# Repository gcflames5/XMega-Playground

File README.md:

XMega Playground
====

Overview
----
This board serves as a place where users can practice various aspects of embedded programming using an XMega(128/64/32)A4U. The first version of this board is focused heavily on testing various types of communication protocols, featuring USB, Serial, CAN, SPI, and I2C. Additionally, the board includes a pair of 7 segment displays, and 10 LEDs (4 are digital RGB LEDs) to allow a degree of output to the user. For use with these various communication protocols, this board includes an separate ADC (with pressure and temperature sensors), flash memory IC, TTL to RS-232 level shifter, CAN transciever, and two IMUs.

List of Features (version 1.0)
----
 - 2 7-segment displays (driven by shift registers)
 - 4 WS2812B digital RHB leds
 - 6 0805 LEDs
 - CAN Transciever
 - RS-232 to TTL level shifter
 - 2 IMUs: Acceleration, Magetometer
 - ADC (w/ 2.5V reference chip)
   - Temperature sensor
   - Ambient pressure sensor
 - Flash Memory
 - Current Sense Op Amp
   - Configurable load for testing

Considerations for Future Versions
----
 - Add a character LCD display for more useful output to the user
 - Break out more GPIO pins into headers
 - Expand number of 7 segment displays
 - Utilize DAC and waveform generation, include H-bridge, microphone, speaker, etc.

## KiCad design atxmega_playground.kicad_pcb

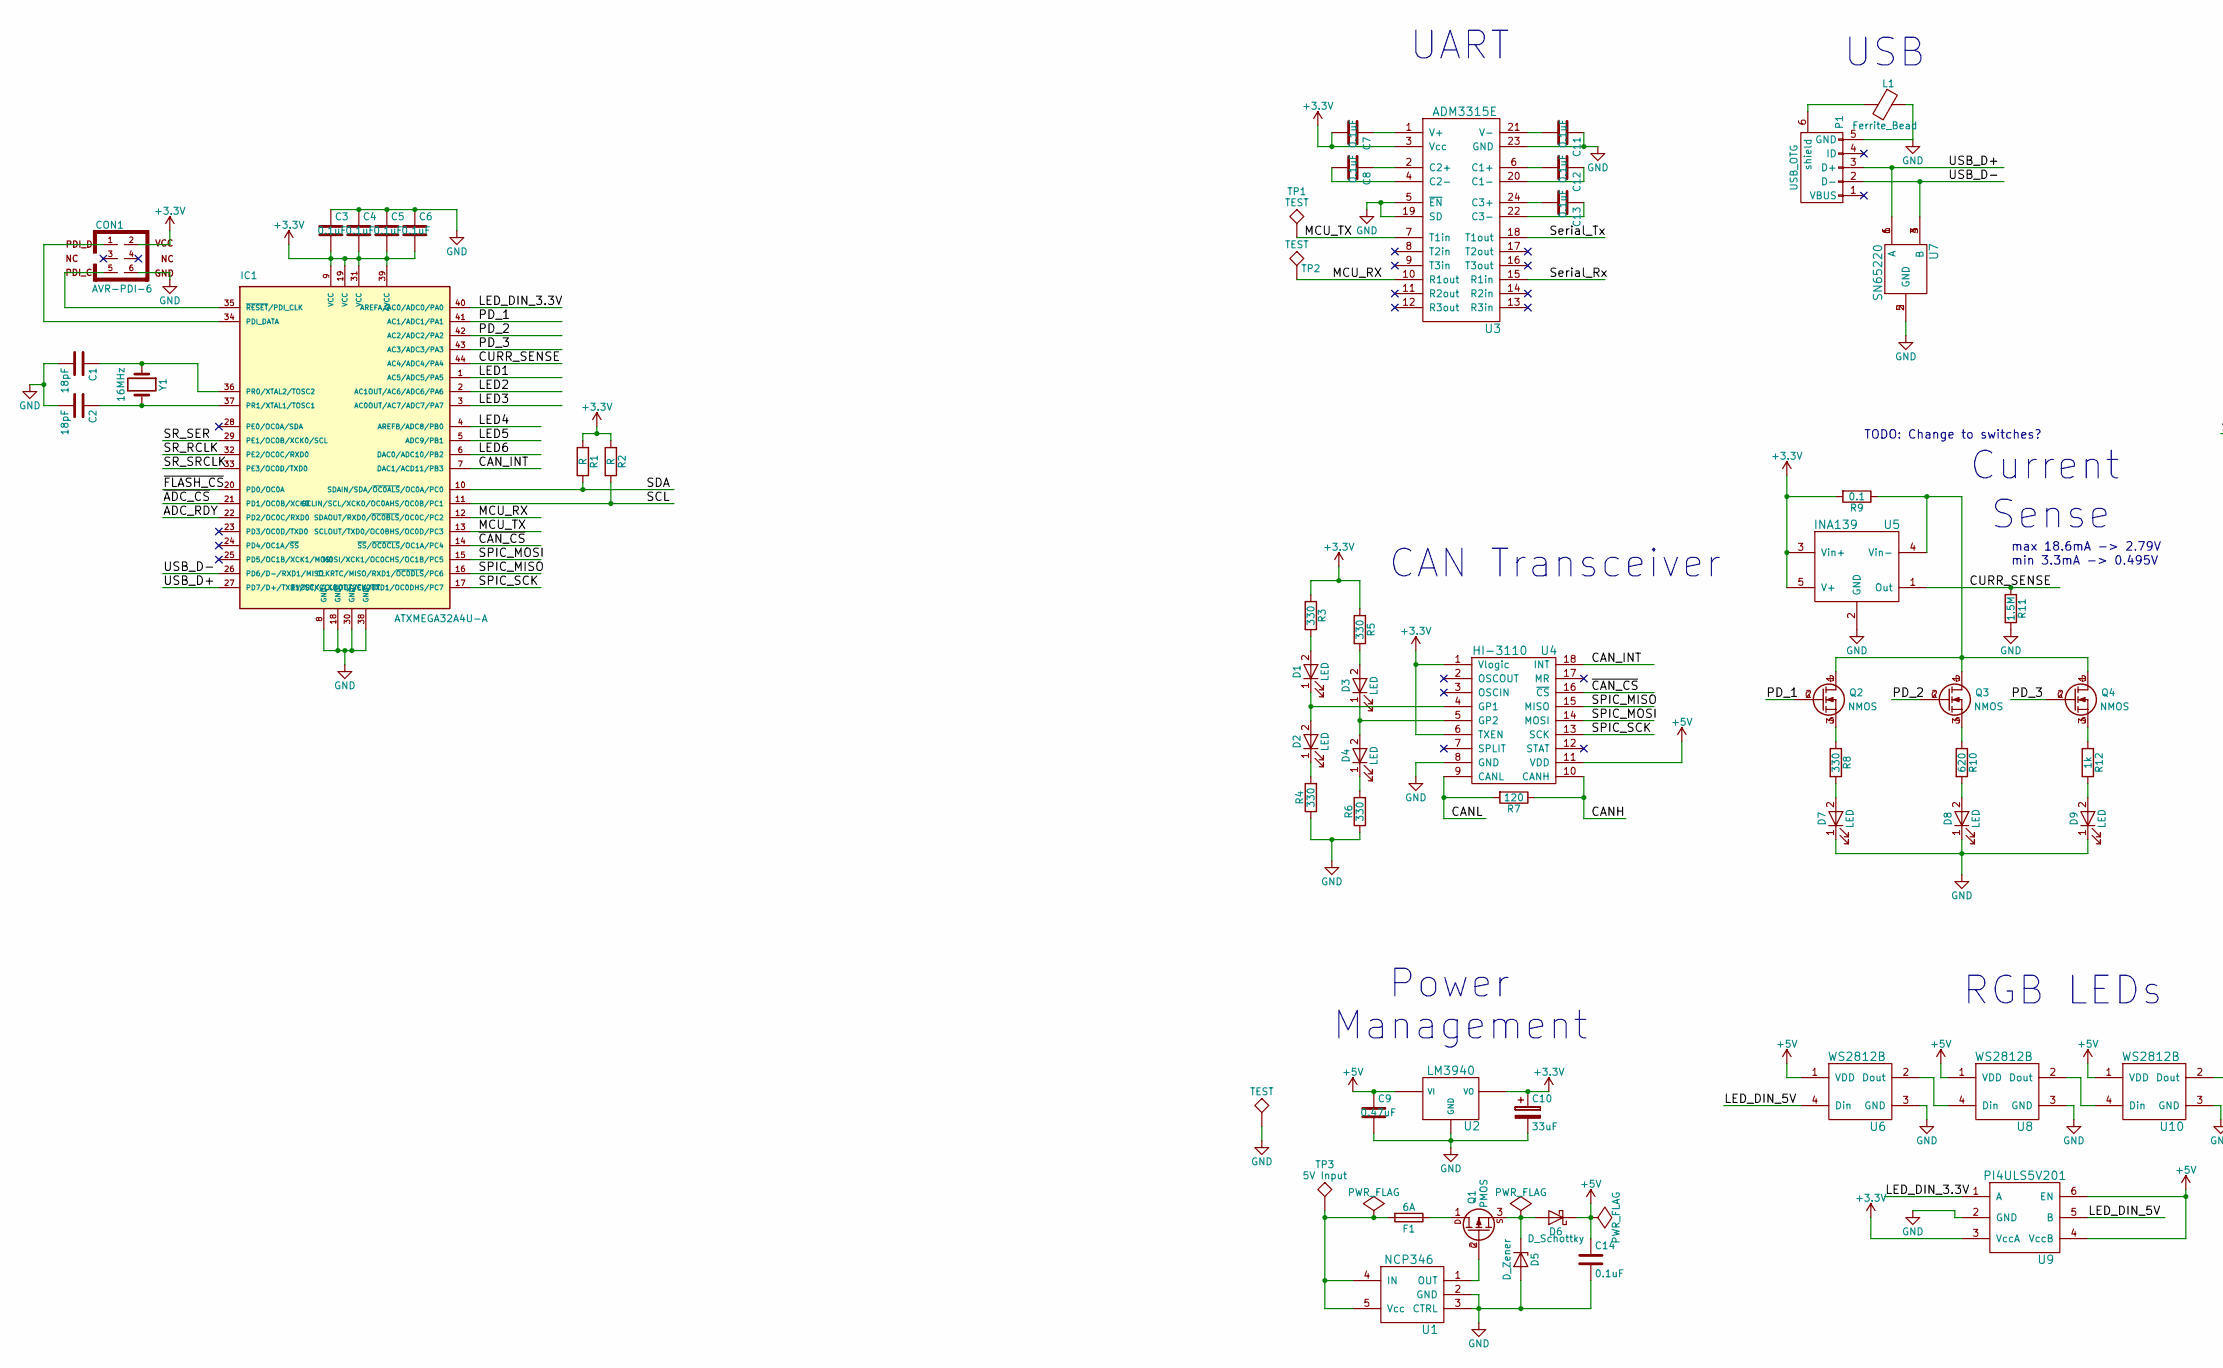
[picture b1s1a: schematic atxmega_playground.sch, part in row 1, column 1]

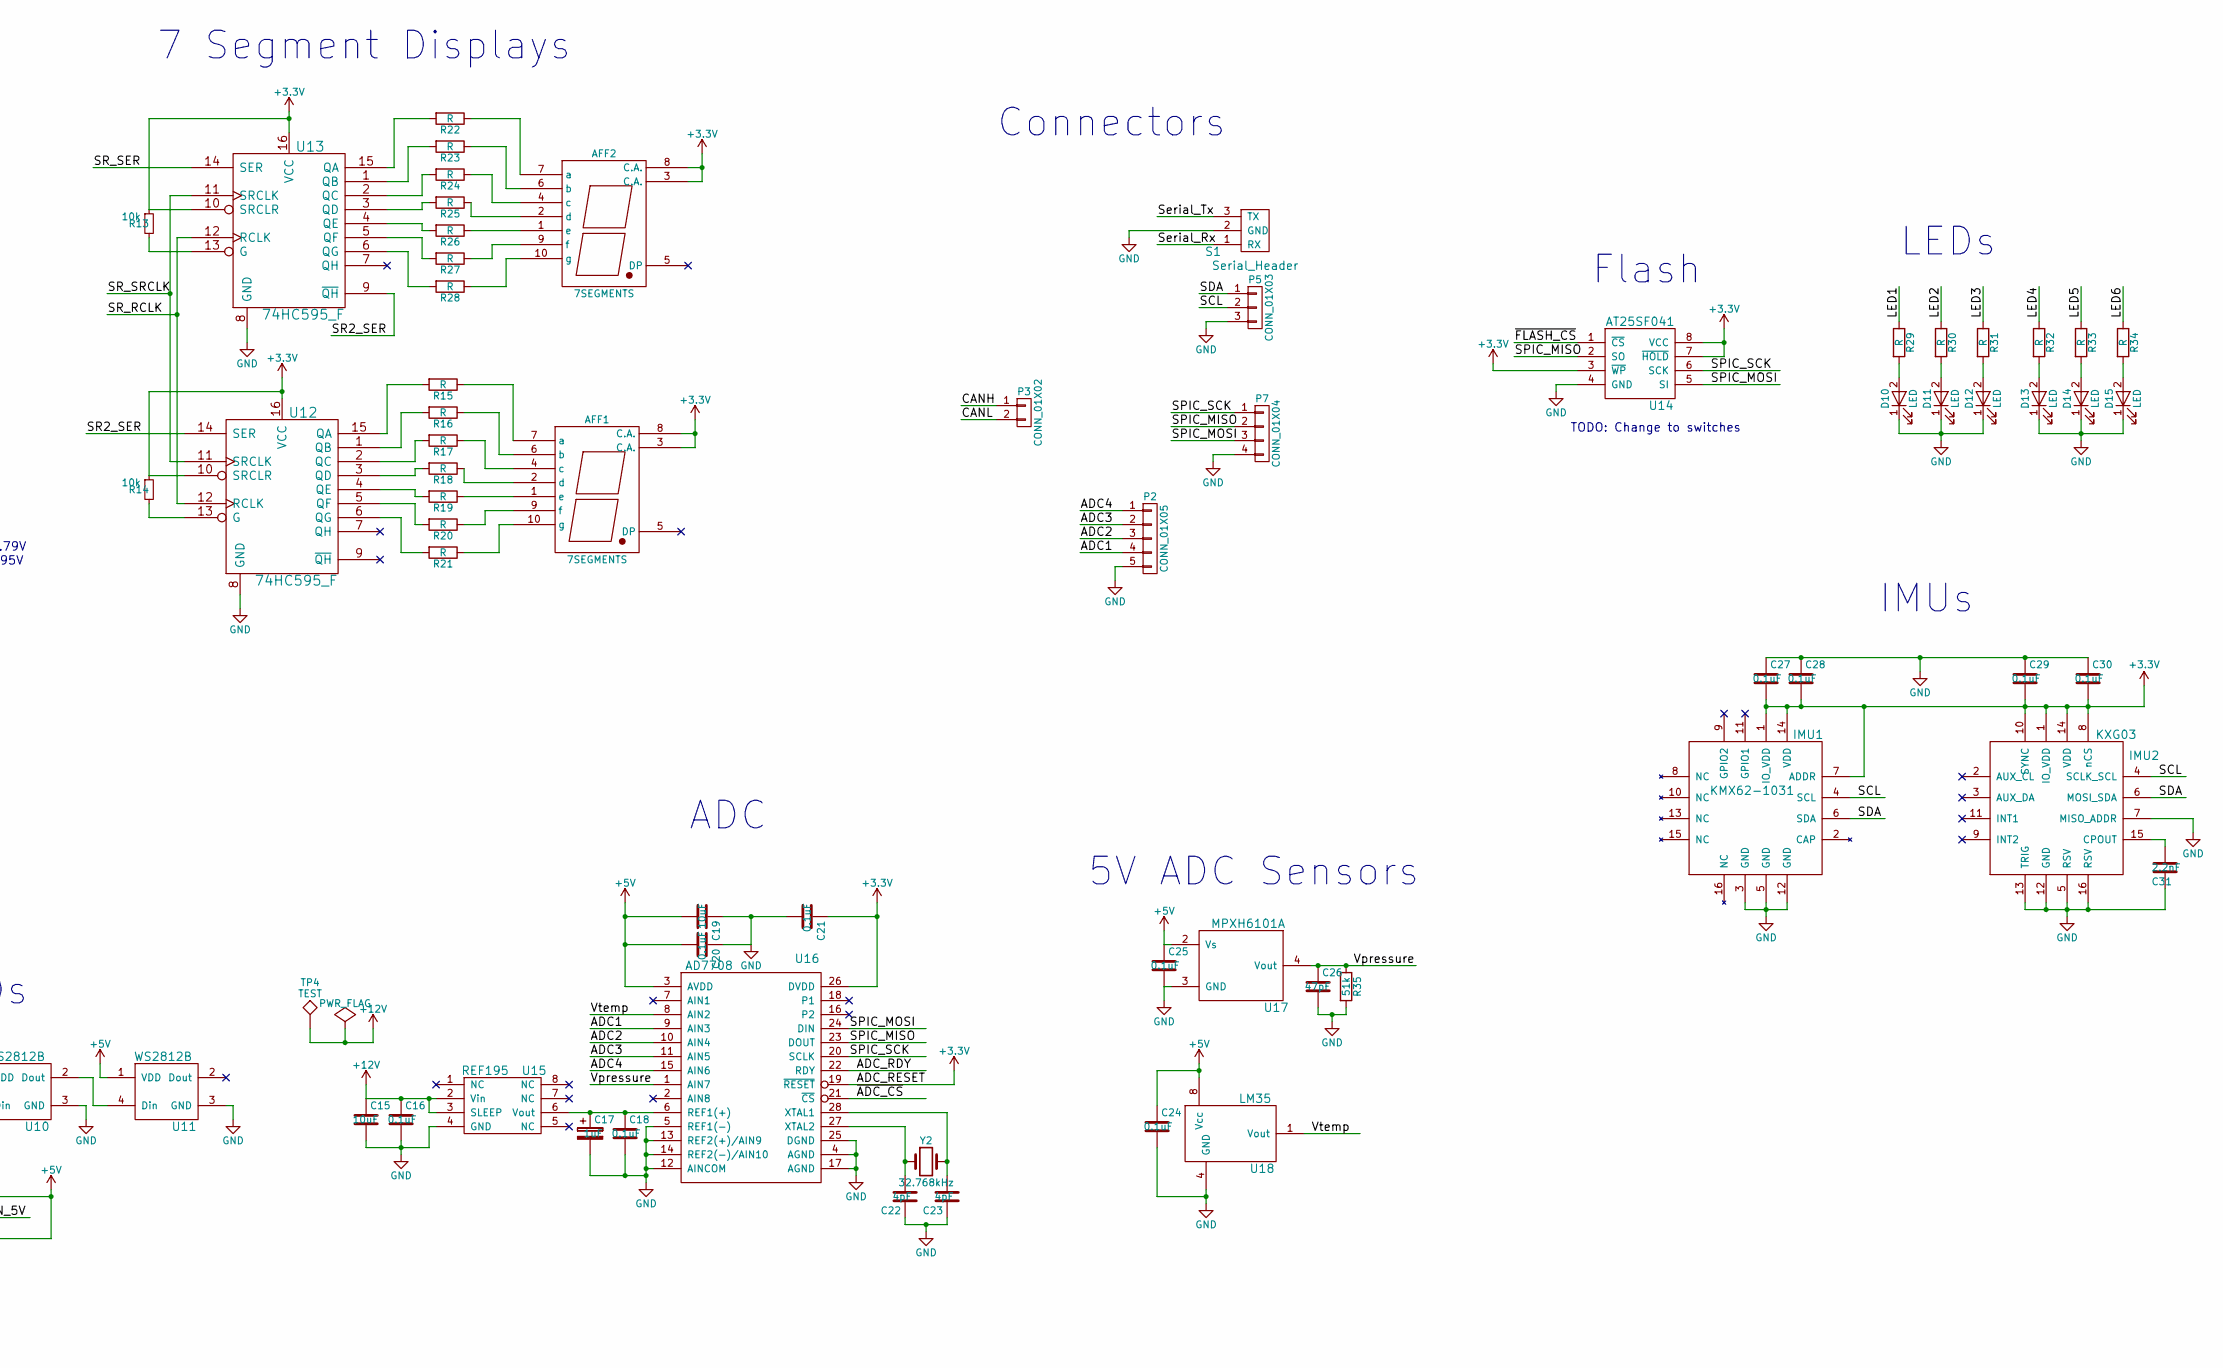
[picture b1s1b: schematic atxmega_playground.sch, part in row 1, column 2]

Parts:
AFF1, AFF2: 7SEGMENTS; 7seg_SC56-11SRWA
C1, C2: 18pF; C_0805
C3, C4, C5, C6, C7, C8, C11, C12, C13, C14, C16, C18, C20, C21, C24, C25, C27, C28, C29, C30: 0.1uF; C_0805
C9: 0.47uF; C_0805
C10: 33uF; R_1206
C15, C19: 10uF; C_0805
C17: 1uF; R_1206
C22, C23: 4pF; C_0805
C26: 47pF; C_0805
C31: 2.2nF; C_0805
CON1: AVR-PDI-6; Pin_Header_Straight_2x03_Pitch2.54mm
D1, D2, D3, D4, D7, D8, D9, D10, D11, D12, D13, D14, D15: LED; LED_0805
D5: D_Zener; SOD-123
D6: D_Schottky; R_0805
F1: 6A; R_1206
IC1: ATXMEGA32A4U-A; TQFP-44_10x10mm_Pitch0.8mm
IMU1: KMX62-1031; KXG03_footprint
IMU2: KXG03; KXG03_footprint
L1: Ferrite_Bead; R_0805
P1: USB_OTG; USB_Mini-B
P2: CONN_01X05; Pin_Header_Straight_1x05_Pitch2.54mm
P3: CONN_01X02; Pin_Header_Straight_1x02_Pitch2.54mm
P5: CONN_01X03; Pin_Header_Straight_1x03_Pitch2.54mm
P7: CONN_01X04; Pin_Header_Straight_1x04_Pitch2.54mm
Q1: PMOS; SOT-23-3_Handsoldering
Q2, Q3, Q4: NMOS; SOT-23-3_Handsoldering
R1, R2, R15, R16, R17, R18, R19, R20, R21, R22, R23, R24, R25, R26, R27, R28, R29, R30, R31, R32, R33, R34: R; R_0805
R3, R4, R5, R6, R8: 330; R_0805
R7: 120; R_0805
R9: 0.1; R_0805
R10: 620; R_0805
R11: 1.5M; R_0805
R12: 1k; R_0805
R13, R14: 10k; R_0805
R35: 51k; R_0805
S1: Serial_Header; Pin_Header_Straight_1x03_Pitch2.54mm
TP1, TP2, TP4, TP5: TEST; TESTPOINT
TP3: 5V Input; TESTPOINT
U1: NCP346; SOT-23-5
U2: LM3940; SOT-223
U3: ADM3315E; TSSOP-24_4.4x7.8mm_Pitch0.65mm
U4: HI-3110; SOIC-18W_7.5x11.6mm_Pitch1.27mm
U5: INA139; SOT-23-5
U6, U8, U10, U11: WS2812B
U7: SN65220; SOT-23-6
U9: PI4ULS5V201; SOT-23-6
U12, U13: 74HC595_F; SOIC-16_3.9x9.9mm_Pitch1.27mm
U14: AT25SF041; SOIC-8_3.9x4.9mm_Pitch1.27mm
U15: REF195; SOIC-8_3.9x4.9mm_Pitch1.27mm
U16: AD7708; SOIC-28W_7.5x17.9mm_Pitch1.27mm
U17: MPXH6101A; SOIC-8_7.5x7.5mm_Pitch1.27mm
U18: LM35; SOIC-8_3.9x4.9mm_Pitch1.27mm
Y1: 16MHz; Crystal_HC49-U_Vertical
Y2: 32.768kHz; R_0805

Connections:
+3V3: AFF1.3 (C.A.), AFF1.8 (C.A.), AFF2.3 (C.A.), AFF2.8 (C.A.), C3.2, C4.2, C5.2, C6.2, C7.2, C10.1, C21.1, C27.2, C28.2, C29.2, C30.2, CON1.2, IC1.9 (VCC), IC1.19 (VCC), IC1.31 (VCC), IC1.39 (AVCC), IMU1.1 (IO_VDD), IMU1.7 (ADDR), IMU1.14 (VDD), IMU2.1 (IO_VDD), IMU2.8 (nCS), IMU2.10 (SYNC), IMU2.14 (VDD), R1.1, R2.1, R3.1, R5.1, R9.2, R13.1, R14.1, U2.3 (VO), U3.3 (Vcc), U4.1 (Vlogic), U4.6 (TXEN), U5.3 (Vin+), U5.5 (V+), U9.3 (VccA), U12.10 (SRCLR), U12.16 (VCC), U13.10 (SRCLR), U13.16 (VCC), U14.3 (~WP), U14.7 (~HOLD), U14.8 (VCC), U16.19 (~RESET), U16.26 (DVDD)
+5V: C9.1, C14.1, C19.2, C20.2, C24.1, C25.1, D6.1 (K), U2.1 (VI), U4.11 (VDD), U6.1 (VDD), U8.1 (VDD), U9.4 (VccB), U9.6 (EN), U10.1 (VDD), U11.1 (VDD), U16.3 (AVDD), U17.2 (Vs), U18.8 (Vcc)
+12V: C15.1, C16.1, TP4.1, U15.2 (Vin), U15.3 (SLEEP)
/ADC1: P2.4, U16.9 (AIN3)
/ADC2: P2.3, U16.10 (AIN4)
/ADC3: P2.2, U16.11 (AIN5)
/ADC4: P2.1, U16.15 (AIN6)
/ADC_RDY: IC1.22 (PD2/OC0C/RXD0), U16.22 (RDY)
/CANH: P3.1, R7.1, U4.10 (CANH)
/CANL: P3.2, R7.2, U4.9 (CANL)
/CAN_INT: IC1.7 (DAC1/ACD11/PB3), U4.18 (INT)
/CURR_SENSE: IC1.44 (AC4/ADC4/PA4), R11.1, U5.1 (Out)
/LED1: IC1.1 (AC5/ADC5/PA5), R29.1
/LED2: IC1.2 (AC1OUT/AC6/ADC6/PA6), R30.1
/LED3: IC1.3 (AC0OUT/AC7/ADC7/PA7), R31.1
/LED4: IC1.4 (AREFB/ADC8/PB0), R32.1
/LED5: IC1.5 (ADC9/PB1), R33.1
/LED6: IC1.6 (DAC0/ADC10/PB2), R34.1
/LED_DIN_3.3V: IC1.40 (AREFA/AC0/ADC0/PA0), U9.1 (A)
/LED_DIN_5V: U6.4 (Din), U9.5 (B)
/MCU_RX: IC1.12 (SDAOUT/RXD0/~OC0BLS~/OC0C/PC2), TP2.1, U3.10 (R1out)
/MCU_TX: IC1.13 (SCLOUT/TXD0/OC0BHS/OC0D/PC3), TP1.1, U3.7 (T1in)
/PD_1: IC1.41 (AC1/ADC1/PA1), Q2.2 (G)
/PD_2: IC1.42 (AC2/ADC2/PA2), Q3.2 (G)
/PD_3: IC1.43 (AC3/ADC3/PA3), Q4.2 (G)
/SCL: IC1.11 (SCLIN/SCL/XCK0/OC0AHS/OC0B/PC1), IMU1.4 (SCL), IMU2.4 (SCLK_SCL), P5.2, R2.2
/SDA: IC1.10 (SDAIN/SDA/~OC0ALS~/OC0A/PC0), IMU1.6 (SDA), IMU2.6 (MOSI_SDA), P5.1, R1.2
/SPIC_MISO: IC1.16 (CLKRTC/MISO/RXD1/~OC0DLS~/PC6), P7.2, U4.15 (MISO), U14.2 (SO), U16.23 (DOUT)
/SPIC_MOSI: IC1.15 (MOSI/XCK1/OC0CHS/OC1B/PC5), P7.3, U4.14 (MOSI), U14.5 (SI), U16.24 (DIN)
/SPIC_SCK: IC1.17 (EVOUT/CLKOUT/SCK/TXD1/OC0DHS/PC7), P7.1, U4.13 (SCK), U14.6 (SCK), U16.20 (SCLK)
/SR2_SER: U12.14 (SER), U13.9 (~QH)
/SR_RCLK: IC1.32 (PE2/OC0C/RXD0), U12.12 (RCLK), U13.12 (RCLK)
/SR_SER: IC1.29 (PE1/OC0B/XCK0/SCL), U13.14 (SER)
/SR_SRCLK: IC1.33 (PE3/OC0D/TXD0), U12.11 (SRCLK), U13.11 (SRCLK)
/Serial_Rx: S1.1 (RX), U3.15 (R1in)
/Serial_Tx: S1.3 (TX), U3.18 (T1out)
/USB_D+: IC1.27 (PD7/D+/TXD1/SCK/CLKOUT/EVOUT), P1.3 (D+), U7.1 (A), U7.6 (A)
/USB_D-: IC1.26 (PD6/D-/RXD1/MISO), P1.2 (D-), U7.3 (B), U7.4 (B)
/Vpressure: C26.1, R35.1, U16.1 (AIN7), U17.4 (Vout)
/Vtemp: U16.8 (AIN2), U18.1 (Vout)
/~ADC_CS: IC1.21 (PD1/OC0B/XCK0), U16.21 (~CS)
/~CAN_CS: IC1.14 (~SS~/~OC0CLS~/OC1A/PC4), U4.16 (~CS)
/~FLASH_CS: IC1.20 (PD0/OC0A), U14.1 (~CS)
GND: C1.2, C2.2, C3.1, C4.1, C5.1, C6.1, C9.2, C10.2, C11.1, C14.2, C15.2, C16.2, C17.2, C18.2, C19.1, C20.1, C21.2, C22.1, C23.1, C24.2, C25.2, C26.2, C27.1, C28.1, C29.1, C30.1, C31.2, CON1.6, D5.2 (A), D7.1 (K), D8.1 (K), D9.1 (K), D10.1 (K), D11.1 (K), D12.1 (K), D13.1 (K), D14.1 (K), D15.1 (K), IC1.8 (GND), IC1.18 (GND), IC1.30 (GND), IC1.38 (GND), IMU1.3 (GND), IMU1.5 (GND), IMU1.12 (GND), IMU2.5 (RSV), IMU2.7 (MISO_ADDR), IMU2.12 (GND), IMU2.13 (TRIG), IMU2.16 (RSV), L1.1, P1.5 (GND), P2.5, P5.3, P7.4, R4.1, R6.1, R11.2, R35.2, S1.2 (GND), TP5.1, U1.2 (GND), U1.3 (CTRL), U2.2 (GND), U2.4 (GND), U3.5 (~EN), U3.19 (SD), U3.23 (GND), U4.8 (GND), U5.2 (GND), U6.3 (GND), U7.2 (GND), U7.5 (GND), U8.3 (GND), U9.2 (GND), U10.3 (GND), U11.3 (GND), U12.8 (GND), U13.8 (GND), U14.4 (GND), U15.4 (GND), U16.4 (AGND), U16.5 (REF1(-)), U16.12 (AINCOM), U16.13 (REF2(+)/AIN9), U16.14 (REF2(-)/AIN10), U16.17 (AGND), U16.25 (DGND), U17.3 (GND), U18.4 (GND)
unnamed: AFF1.1 (e), R19.1
unnamed: AFF1.2 (d), R18.1
unnamed: AFF1.4 (c), R17.1
unnamed: AFF1.6 (b), R16.1
unnamed: AFF1.7 (a), R15.1
unnamed: AFF1.9 (f), R20.1
unnamed: AFF1.10 (g), R21.1
unnamed: AFF2.1 (e), R26.1
unnamed: AFF2.2 (d), R25.1
unnamed: AFF2.4 (c), R24.1
unnamed: AFF2.6 (b), R23.1
unnamed: AFF2.7 (a), R22.1
unnamed: AFF2.9 (f), R27.1
unnamed: AFF2.10 (g), R28.1
unnamed: C1.1, IC1.36 (PR0/XTAL2/TOSC2), Y1.1
unnamed: C2.1, IC1.37 (PR1/XTAL1/TOSC1), Y1.2
unnamed: C7.1, U3.1 (V+)
unnamed: C8.1, U3.2 (C2+)
unnamed: C8.2, U3.4 (C2-)
unnamed: C11.2, U3.21 (V-)
unnamed: C12.1, U3.20 (C1-)
unnamed: C12.2, U3.6 (C1+)
unnamed: C13.1, U3.22 (C3-)
unnamed: C13.2, U3.24 (C3+)
unnamed: C17.1, C18.1, U15.6 (Vout), U16.6 (REF1(+))
unnamed: C22.2, U16.27 (XTAL2), Y2.1
unnamed: C23.2, U16.28 (XTAL1), Y2.2
unnamed: C31.1, IMU2.15 (CPOUT)
unnamed: CON1.1, IC1.34 (PDI_DATA)
unnamed: CON1.5, IC1.35 (~RESET~/PDI_CLK)
unnamed: D1.1 (K), D2.2 (A), U4.4 (GP1)
unnamed: D1.2 (A), R3.2
unnamed: D2.1 (K), R4.2
unnamed: D3.1 (K), D4.2 (A), U4.5 (GP2)
unnamed: D3.2 (A), R5.2
unnamed: D4.1 (K), R6.2
unnamed: D5.1 (K), D6.2 (A), Q1.3 (S)
unnamed: D7.2 (A), R8.2
unnamed: D8.2 (A), R10.2
unnamed: D9.2 (A), R12.2
unnamed: D10.2 (A), R29.2
unnamed: D11.2 (A), R30.2
unnamed: D12.2 (A), R31.2
unnamed: D13.2 (A), R32.2
unnamed: D14.2 (A), R33.2
unnamed: D15.2 (A), R34.2
unnamed: F1.1, Q1.1 (D)
unnamed: F1.2, TP3.1, U1.4 (IN), U1.5 (Vcc)
unnamed: L1.2, P1.6 (shield)
unnamed: Q1.2 (G), U1.1 (OUT)
unnamed: Q2.1 (D), Q3.1 (D), Q4.1 (D), R9.1, U5.4 (Vin-)
unnamed: Q2.3 (S), R8.1
unnamed: Q3.3 (S), R10.1
unnamed: Q4.3 (S), R12.1
unnamed: R13.2, U13.13 (G)
unnamed: R14.2, U12.13 (G)
unnamed: R15.2, U12.15 (QA)
unnamed: R16.2, U12.1 (QB)
unnamed: R17.2, U12.2 (QC)
unnamed: R18.2, U12.3 (QD)
unnamed: R19.2, U12.4 (QE)
unnamed: R20.2, U12.5 (QF)
unnamed: R21.2, U12.6 (QG)
unnamed: R22.2, U13.15 (QA)
unnamed: R23.2, U13.1 (QB)
unnamed: R24.2, U13.2 (QC)
unnamed: R25.2, U13.3 (QD)
unnamed: R26.2, U13.4 (QE)
unnamed: R27.2, U13.5 (QF)
unnamed: R28.2, U13.6 (QG)
unnamed: U6.2 (Dout), U8.4 (Din)
unnamed: U10.2 (Dout), U11.4 (Din)
unnamed: U8.2 (Dout), U10.4 (Din)

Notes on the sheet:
UART
CAN Transceiver
USB
Current
Sense
max 18.6mA -> 2.79V
min 3.3mA -> 0.495V
TODO: Change to switches?
7 Segment Displays
TODO: Change to switches
Flash
Power
Management
RGB LEDs
LEDs
Connectors
ADC
5V ADC Sensors
IMUs

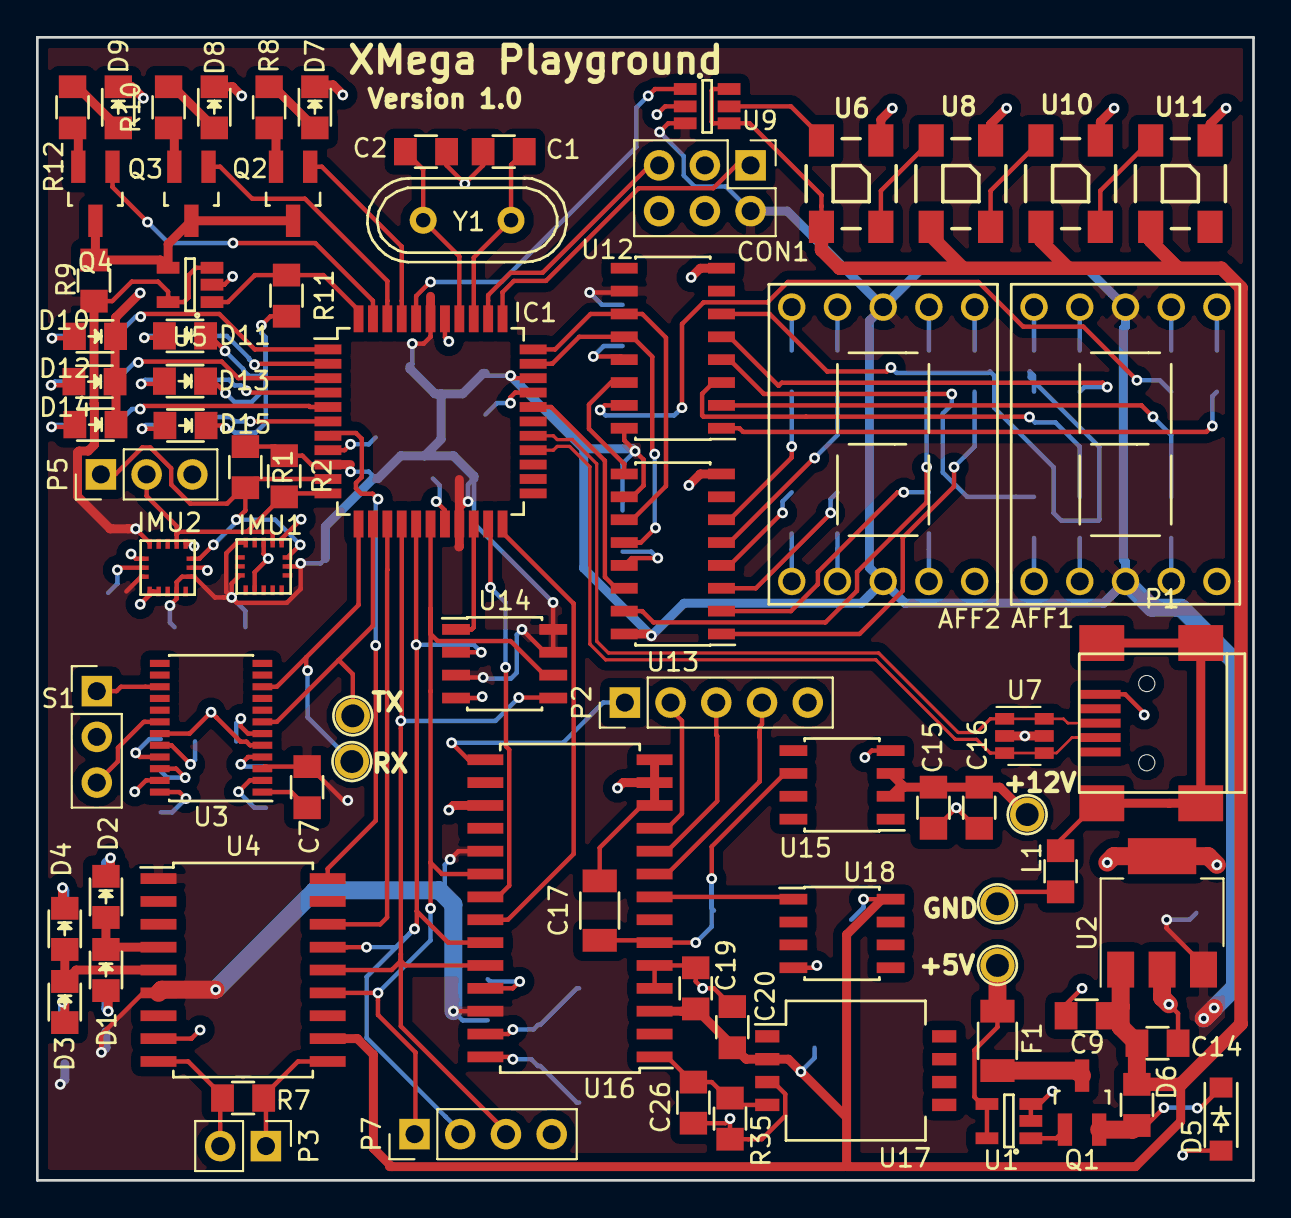
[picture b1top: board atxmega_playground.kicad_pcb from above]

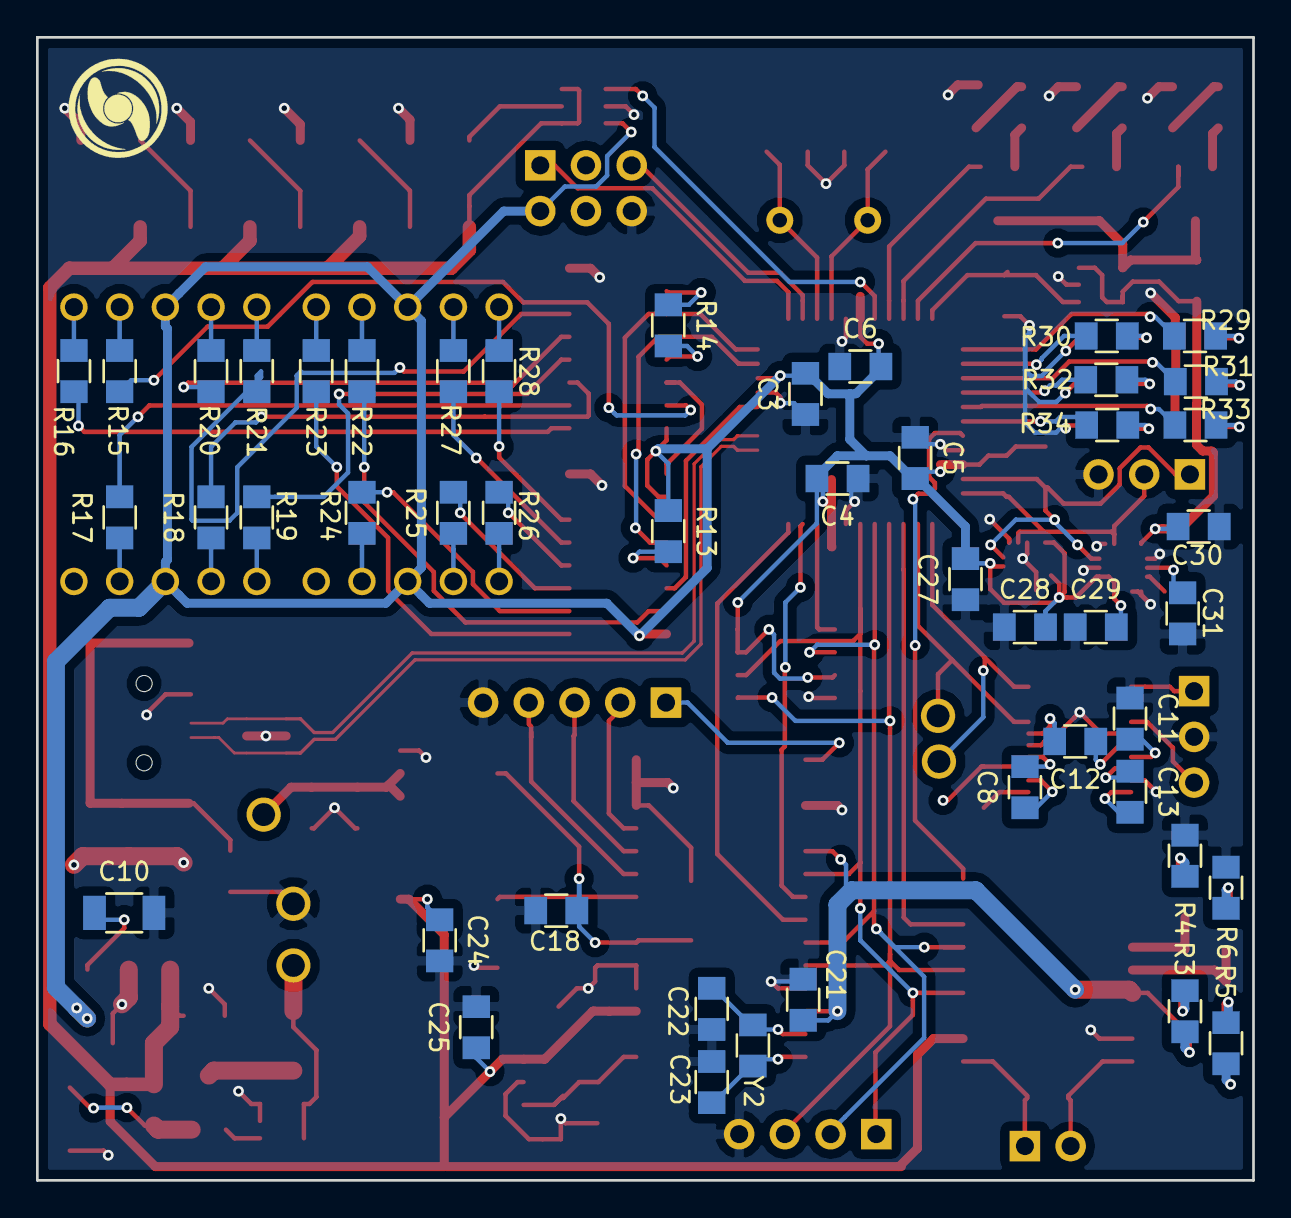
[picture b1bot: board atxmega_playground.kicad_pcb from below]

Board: 2 copper layers, 67.6 x 63.5 mm, 124 parts (47 on the bottom side), 117 nets.

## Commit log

2017-01-06 Initial Commit: empty project and readme
2017-01-07 Add 3.3V ttl to +/- 10V RS-232 level shifter
2017-01-07 Add HI-3110 CAN Transceiver
2017-01-07 Add USB and Current Sense
2017-01-07 Fix current sense voltage calculations
2017-01-07 Add 74HC595 shift register and LEDs
2017-01-07 Drive 2 7-seg displays via shift registers, add flash memory
2017-01-08 Add a few i2c sensors, power management circuitry, and digital RGB LEDs
2017-01-08 Fill out MCU pins, add LEDs, (and digital pot maybe?)
2017-01-08 Add breakout connectors
2017-01-08 Begin assigning footprints
2017-01-08 More footprints, beginning stages of layout
2017-01-09 Add GPIO's ADC and 5V sensors, 7seg display footprint, and HIM's IMU's
2017-01-10 Basic layout, component positions mostly final
2017-01-10 Initial layout complete, no DRC errors or unconnected tracks
2017-01-10 Move refdes text
2017-01-10 Final touches
2017-01-10 First revision, finalized!
